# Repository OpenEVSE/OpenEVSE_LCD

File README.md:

# OpenEVSE_LCD
OpenEVSE_LCD  - Original version

OpenEVSE_LCD+RTC - Added Real Time Clock

OpenEVSE_LCD+RTCv2 - Smaller form factor

OpenEVSE_LCD+RTCv3 - changes pot VR-1 to fixed resistance

OpenEVSE_LCD+RTCv4 - Added dedicated temp sensor so LCD can be built with or without RTC and still provide temperature to OpenEVSE controller. Moved ports to opposite side to allign better with OpenEVSE controller low voltage position. Changed connector type to semi locking and polorized JST to prevent reverse connection durring assembly.

OpenEVSE_SmartLCD Experimental - not Tested adds microprocessor to remove UI load from OpenEVSE - RAPI

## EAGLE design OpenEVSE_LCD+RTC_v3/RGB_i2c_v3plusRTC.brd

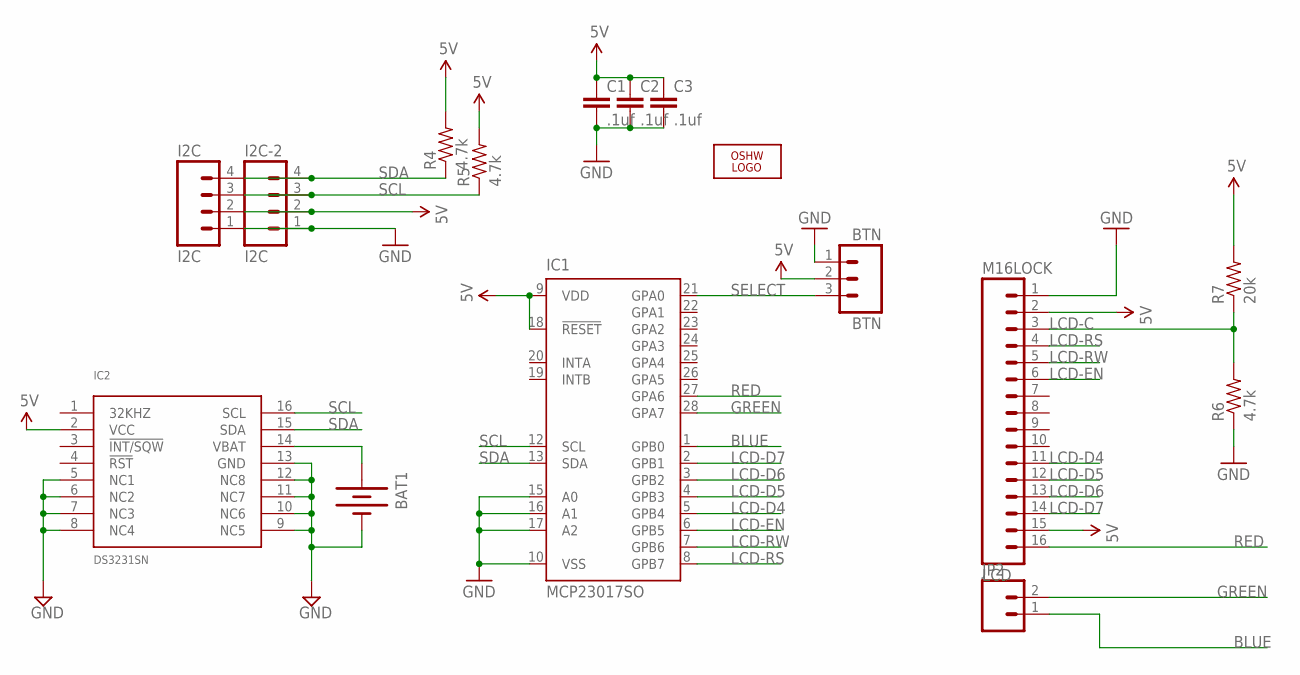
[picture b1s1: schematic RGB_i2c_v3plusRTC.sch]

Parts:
BAT1: BATTERY12MM; BATTCON_12MM
BTN: BTN; 1X03_LOCK
C1, C2, C3: .1uf; 0805
I2C, I2C-2: I2C; 1X04_LOCK
IC1: MCP23017SO; SO28W
IC2: DS3231SN; SO16W
JP2: M02PTH; 1X02
LCD: M16LOCK; 1X16_LOCK
LOGO2: OSHW_LOGO_10MILX0350-NT; OSHW_10X350_NOTEXT
R4, R5, R6: 4.7k; 0805
R7: 20k; 0805

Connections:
5V: BTN.2, C1.1, C2.1, C3.1, I2C.2, I2C-2.2, IC1.9 (VDD), IC1.18 (!RESET), IC2.2 (VCC), LCD.2, LCD.15, R4.2, R5.2, R7.2
BLUE: IC1.1 (GPB0), JP2.1
GND: BAT1.GND (-), BTN.1, C1.2, C2.2, C3.2, I2C.1, I2C-2.1, IC1.10 (VSS), IC1.15 (A0), IC1.16 (A1), IC1.17 (A2), IC2.5 (NC1), IC2.6 (NC2), IC2.7 (NC3), IC2.8 (NC4), IC2.9 (NC5), IC2.10 (NC6), IC2.11 (NC7), IC2.12 (NC8), IC2.13 (GND), LCD.1, R6.1
GREEN: IC1.28 (GPA7), JP2.2
LCD-C: LCD.3, R6.2, R7.1
LCD-D4: IC1.5 (GPB4), LCD.11
LCD-D5: IC1.4 (GPB3), LCD.12
LCD-D6: IC1.3 (GPB2), LCD.13
LCD-D7: IC1.2 (GPB1), LCD.14
LCD-EN: IC1.6 (GPB5), LCD.6
LCD-RS: IC1.8 (GPB7), LCD.4
LCD-RW: IC1.7 (GPB6), LCD.5
unnamed: BAT1.PWR@1 (+), IC2.14 (VBAT)
RED: IC1.27 (GPA6), LCD.16
SCL: I2C.3, I2C-2.3, IC1.12 (SCL), IC2.16 (SCL), R5.1
SDA: I2C.4, I2C-2.4, IC1.13 (SDA), IC2.15 (SDA), R4.1
SELECT: BTN.3, IC1.21 (GPA0)

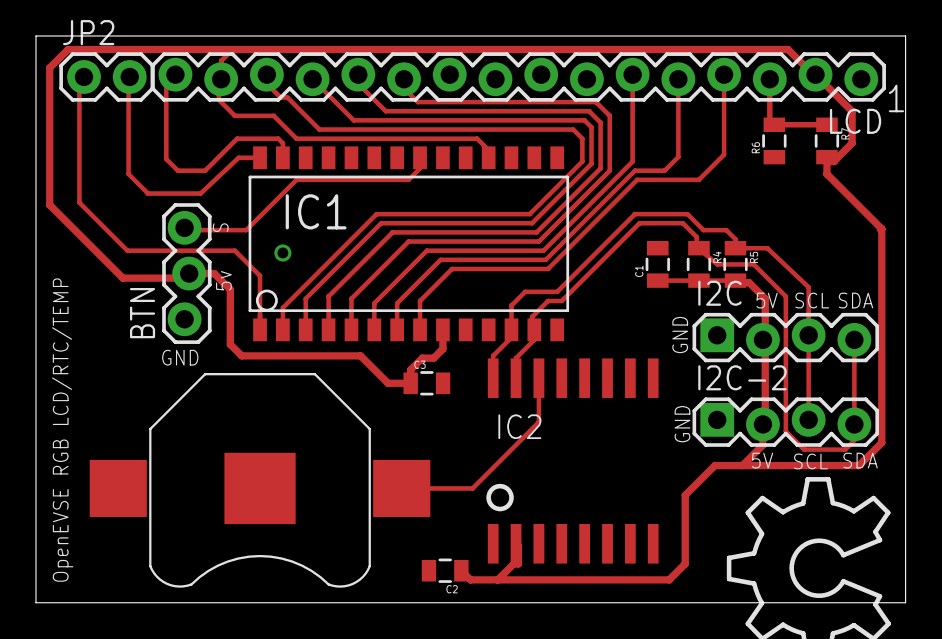
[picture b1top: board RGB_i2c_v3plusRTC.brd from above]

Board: 2 copper layers, 48.3 x 31.5 mm, 16 parts (0 on the bottom side), 17 nets.

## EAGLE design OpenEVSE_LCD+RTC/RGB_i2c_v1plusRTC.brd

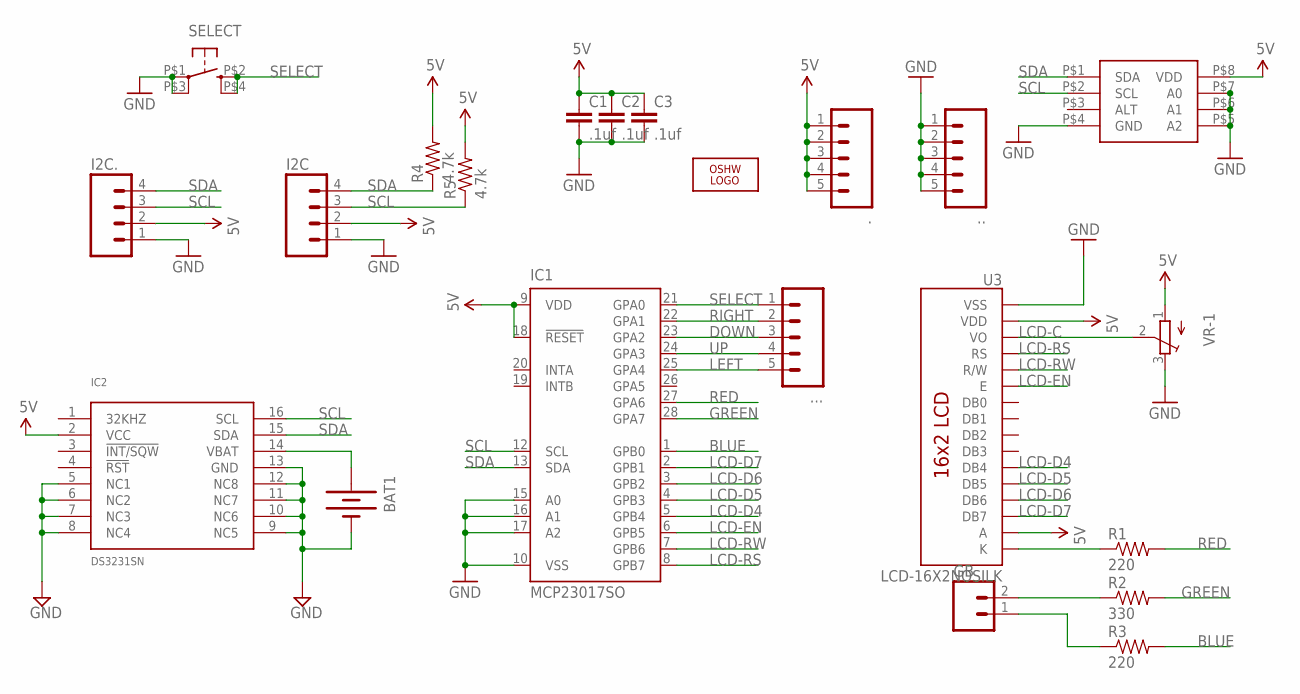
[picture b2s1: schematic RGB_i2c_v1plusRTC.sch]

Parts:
., .., ...: M05LOCK; 1X05_LOCK
BAT1: BATTERY12MM; BATTCON_12MM
C1, C2, C3: .1uf; 0805
GB: M02LOCK; 1X02_LOCK
I2C, I2C.: M04LOCK; 1X04_LOCK
IC1: MCP23017SO; SO28W
IC2: DS3231SN; SO16W
IC3: MCP9808; MSOP8
LOGO2: OSHW_LOGO_10MILX0350-NT; OSHW_10X350_NOTEXT
R1, R3: 220; 0805
R2: 330; 0805
R4, R5: 4.7k; 0805
SELECT: KMR211GLFS; PUSHBUTTON-KMR241GLFS
U3: LCD-16X2NOSILK; LCD-16X2_NOSILK
VR-1: TRIMPOTTC33X; TC33X

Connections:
5V: ..1, ..2, ..3, ..4, ..5, C1.1, C2.1, C3.1, I2C.2, I2C..2, IC1.9 (VDD), IC1.18 (!RESET), IC2.2 (VCC), IC3.P$8 (VDD), R4.2, R5.2, U3.2 (VDD), U3.15 (A), VR-1.1 (A)
BLUE: IC1.1 (GPB0), R3.2
DOWN: ....3, IC1.23 (GPA2)
GND: ...1, ...2, ...3, ...4, ...5, BAT1.GND (-), C1.2, C2.2, C3.2, I2C.1, I2C..1, IC1.10 (VSS), IC1.15 (A0), IC1.16 (A1), IC1.17 (A2), IC2.5 (NC1), IC2.6 (NC2), IC2.7 (NC3), IC2.8 (NC4), IC2.9 (NC5), IC2.10 (NC6), IC2.11 (NC7), IC2.12 (NC8), IC2.13 (GND), IC3.P$4 (GND), SELECT.P$1 (1), SELECT.P$3 (3), U3.1 (VSS), VR-1.3 (E)
GREEN: IC1.28 (GPA7), R2.2
LCD-C: U3.3 (VO), VR-1.2 (S)
LCD-D4: IC1.5 (GPB4), U3.11 (DB4)
LCD-D5: IC1.4 (GPB3), U3.12 (DB5)
LCD-D6: IC1.3 (GPB2), U3.13 (DB6)
LCD-D7: IC1.2 (GPB1), U3.14 (DB7)
LCD-EN: IC1.6 (GPB5), U3.6 (E)
LCD-RS: IC1.8 (GPB7), U3.4 (RS)
LCD-RW: IC1.7 (GPB6), U3.5 (R/W)
LEFT: ....5, IC1.25 (GPA4)
unnamed: GB.2, R2.1
unnamed: GB.1, R3.1
unnamed: BAT1.PWR@1 (+), IC2.14 (VBAT)
unnamed: R1.1, U3.16 (K)
unnamed: IC3.P$5 (A2), IC3.P$6 (A1), IC3.P$7 (A0)
RED: IC1.27 (GPA6), R1.2
RIGHT: ....2, IC1.22 (GPA1)
SCL: I2C.3, I2C..3, IC1.12 (SCL), IC2.16 (SCL), IC3.P$2 (SCL), R5.1
SDA: I2C.4, I2C..4, IC1.13 (SDA), IC2.15 (SDA), IC3.P$1 (SDA), R4.1
SELECT: ....1, IC1.21 (GPA0), SELECT.P$2 (2), SELECT.P$4 (4)
UP: ....4, IC1.24 (GPA3)

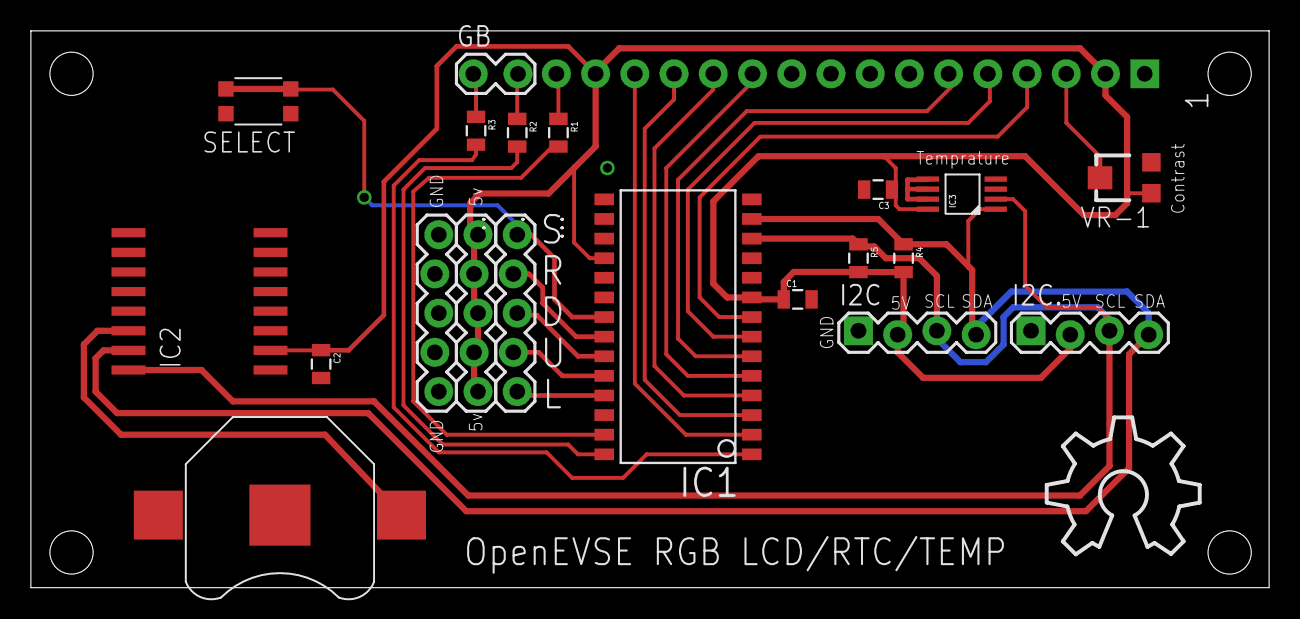
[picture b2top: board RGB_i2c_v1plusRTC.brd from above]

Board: 2 copper layers, 80.2 x 36.1 mm, 22 parts (1 on the bottom side), 25 nets.

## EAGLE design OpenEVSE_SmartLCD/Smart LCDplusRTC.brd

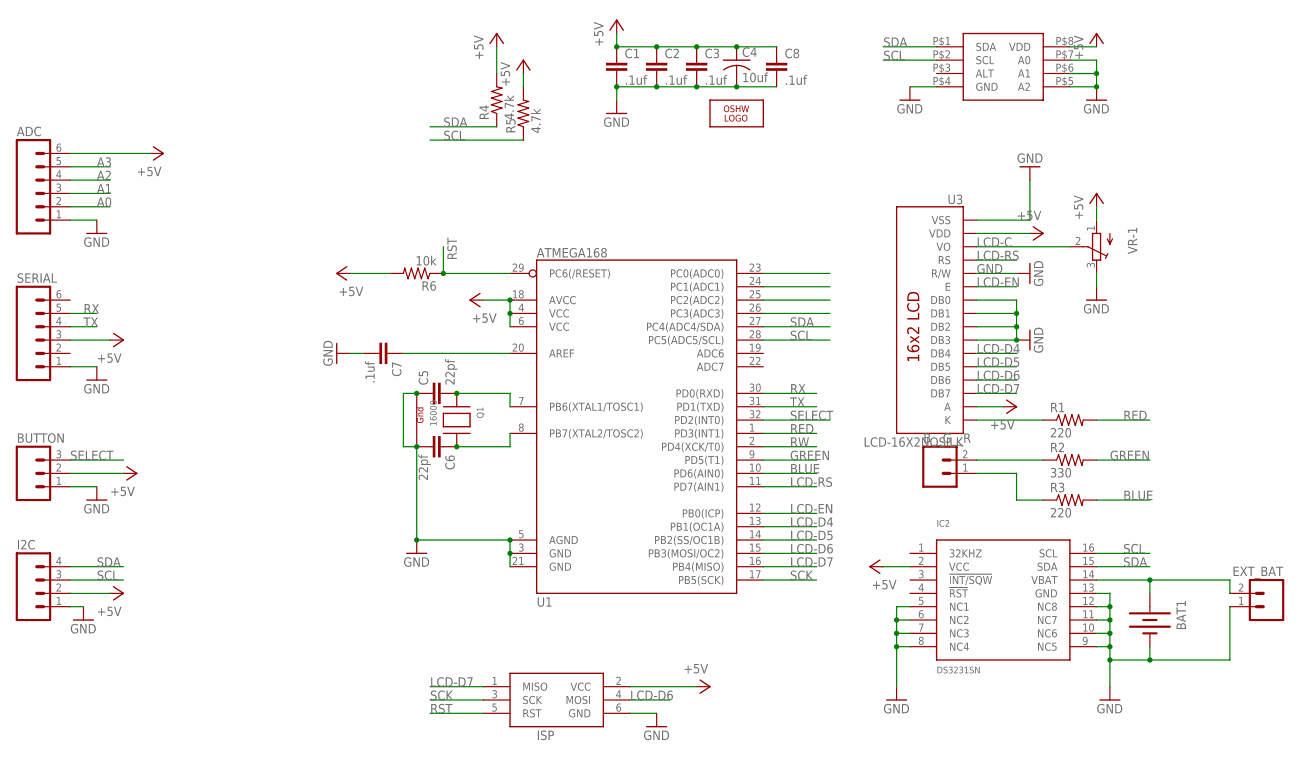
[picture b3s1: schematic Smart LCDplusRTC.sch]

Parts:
ADC: M06SIP_LOCK; 1X06-SIP_LOCK
BAT1: BATTERY12MM; BATTCON_12MM
BUTTON: M03LOCK; 1X03_LOCK
B__G__R: M02LOCK; 1X02_LOCK
C1, C2, C3, C7, C8: .1uf; 0805
C4: 10uf; C1206
C5, C6: 22pf; 0805
EXT_BAT: M02LOCK; 1X02_LOCK
I2C: M04LOCK; 1X04_LOCK
IC2: DS3231SN; SO16W
ISP: AVRISP-6; AVRISP
LOGO2: OSHW_LOGO_10MILX0350-NT; OSHW_10X350_NOTEXT
Q1: 16000; NX3225
R1, R3: 220; 0805
R2: 330; 0805
R4, R5: 4.7k; 0805
R6: 10k; 0805
SERIAL: M06LOCK; 1X06_LOCK
U1: ATMEGA168; TQFP32-08
U3: LCD-16X2NOSILK; LCD-16X2_NOSILK
U$1: MCP9808; MSOP8
VR-1: TRIMPOTTC33X; TC33X

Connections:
+5V: ADC.6, BUTTON.2, C1.1, C2.1, C3.1, C4.1, C8.1, I2C.2, IC2.2 (VCC), ISP.2 (VCC), R4.2, R5.2, R6.2, SERIAL.3, U1.4 (VCC), U1.6 (VCC), U1.18 (AVCC), U3.2 (VDD), U3.15 (A), U$1.P$8 (VDD), VR-1.1 (A)
A0: ADC.2, U1.23 (PC0(ADC0))
A1: ADC.3, U1.24 (PC1(ADC1))
A2: ADC.4, U1.25 (PC2(ADC2))
A3: ADC.5, U1.26 (PC3(ADC3))
BLUE: R3.2, U1.10 (PD6(AIN0))
GND: ADC.1, BAT1.GND (-), BUTTON.1, C1.2, C2.2, C3.2, C4.2, C5.1, C6.2, C7.2, C8.2, EXT_BAT.1, I2C.1, IC2.5 (NC1), IC2.6 (NC2), IC2.7 (NC3), IC2.8 (NC4), IC2.9 (NC5), IC2.10 (NC6), IC2.11 (NC7), IC2.12 (NC8), IC2.13 (GND), ISP.6 (GND), Q1.1 (G1), Q1.3 (G2), SERIAL.1, U1.3 (GND), U1.5 (AGND), U1.21 (GND), U3.1 (VSS), U3.5 (R/W), U3.7 (DB0), U3.8 (DB1), U3.9 (DB2), U3.10 (DB3), U$1.P$4 (GND), U$1.P$5 (A2), U$1.P$6 (A1), U$1.P$7 (A0), VR-1.3 (E)
GREEN: R2.2, U1.9 (PD5(T1))
LCD-C: U3.3 (VO), VR-1.2 (S)
LCD-D4: U1.13 (PB1(OC1A)), U3.11 (DB4)
LCD-D5: U1.14 (PB2(SS/OC1B)), U3.12 (DB5)
LCD-D6: ISP.4 (MOSI), U1.15 (PB3(MOSI/OC2)), U3.13 (DB6)
LCD-D7: ISP.1 (MISO), U1.16 (PB4(MISO)), U3.14 (DB7)
LCD-EN: U1.12 (PB0(ICP)), U3.6 (E)
LCD-RS: U1.11 (PD7(AIN1)), U3.4 (RS)
unnamed: B__G__R.2, R2.1
unnamed: B__G__R.1, R3.1
unnamed: BAT1.PWR@1 (+), EXT_BAT.2, IC2.14 (VBAT)
unnamed: R1.1, U3.16 (K)
unnamed: C5.2, Q1.2 (X1), U1.7 (PB6(XTAL1/TOSC1))
unnamed: C6.1, Q1.4 (X2), U1.8 (PB7(XTAL2/TOSC2))
unnamed: C7.1, U1.20 (AREF)
RED: R1.2, U1.1 (PD3(INT1))
RST: ISP.5 (RST), R6.1, U1.29 (PC6(/RESET))
RW: U1.2 (PD4(XCK/T0))
RX: SERIAL.5, U1.30 (PD0(RXD))
SCK: ISP.3 (SCK), U1.17 (PB5(SCK))
SCL: I2C.3, IC2.16 (SCL), R5.1, U1.28 (PC5(ADC5/SCL)), U$1.P$2 (SCL)
SDA: I2C.4, IC2.15 (SDA), R4.1, U1.27 (PC4(ADC4/SDA)), U$1.P$1 (SDA)
SELECT: BUTTON.3, U1.32 (PD2(INT0))
TX: SERIAL.4, U1.31 (PD1(TXD))

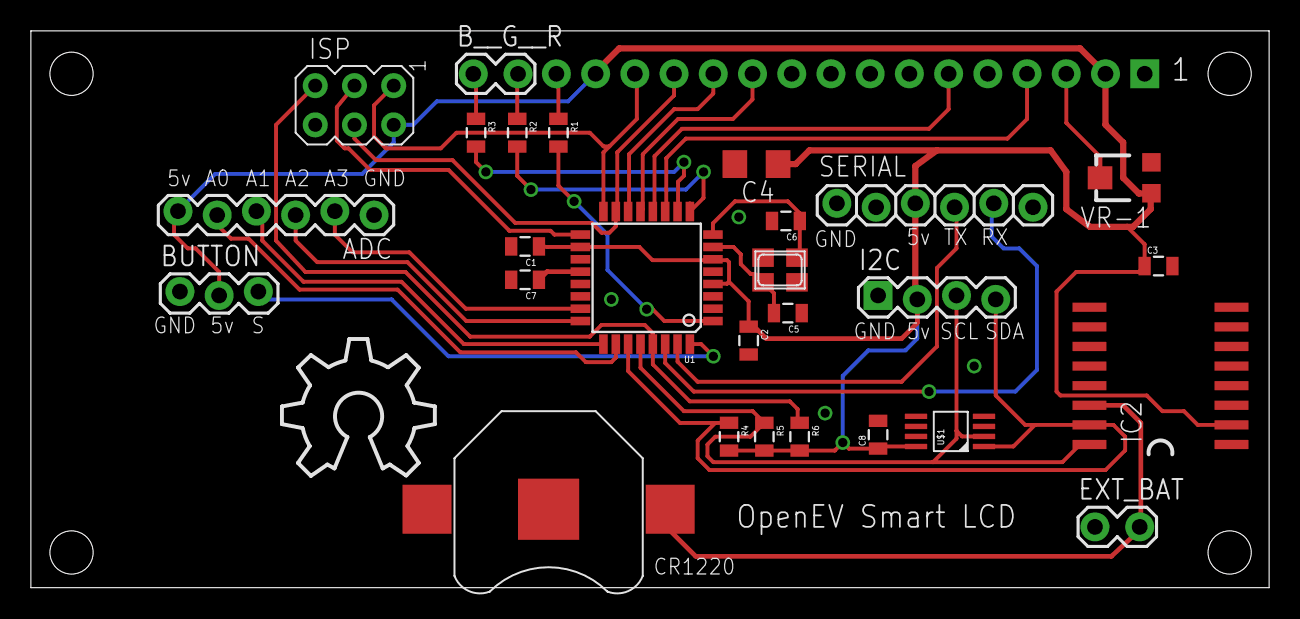
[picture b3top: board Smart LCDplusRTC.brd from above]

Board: 2 copper layers, 80.2 x 36.1 mm, 29 parts (1 on the bottom side), 30 nets.

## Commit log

2015-10-09 :neckbeard: Added .gitattributes & .gitignore files
2015-10-09 OpenEVSE LCD
2015-10-09 README.md
2016-11-24 Add Mono LCD with MSP9808 Temp Sensor
2020-06-18 added schematic pdf to RGB_i2c_v2plustRTC
2021-01-12 Upload v3 and v4
2021-01-12 Update Readme for v4
